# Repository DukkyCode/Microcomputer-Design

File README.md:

# Microcomputer Design
Introduction:
-	The goal of this project is to design, build, and program a single-board computer. It also provides insight into computer architecture

Chip Specification:
- XR68C681CJ-F – DUART: the XR68C681 devices offers a single IC solution for the 68000 family of microprocessors.
- U62256ADK07LLG – RAM: Static RAM 32K x 8-Bit High Speed CMOS 150ns DIP -28
- AT28C256-15PU – ROM: Memory & Data Storage (EEPROM IC EEPROM 256k 50NS 28DIP) 
- Max232E: IC Transceiver 2 channel 16DIP to interface with DUART
- LD1085V50 – Voltage Regulator: Step 9V down to 5V to provide power for the entire board
- JS202011SCQN – Power Switch: Switch to turn on & off power
- B3F-1022 – Reset Button: Simple power button to activate RESET on the buttons
-	A-DS 09 A/KG-T2S – D-SUB connector: create serial communications with the desktop
-	PJ-002B – Barrel Plug: Barrel Connector to connect with power adapter
- ECS-2200B-080: Create 8MHz clock signal for the CPLD & CPU
- ECS-2100AX-036: Create 3.6MHz clock signal for the DUART chips
- 22-28-4061: J-TAG connector to program the CPLD

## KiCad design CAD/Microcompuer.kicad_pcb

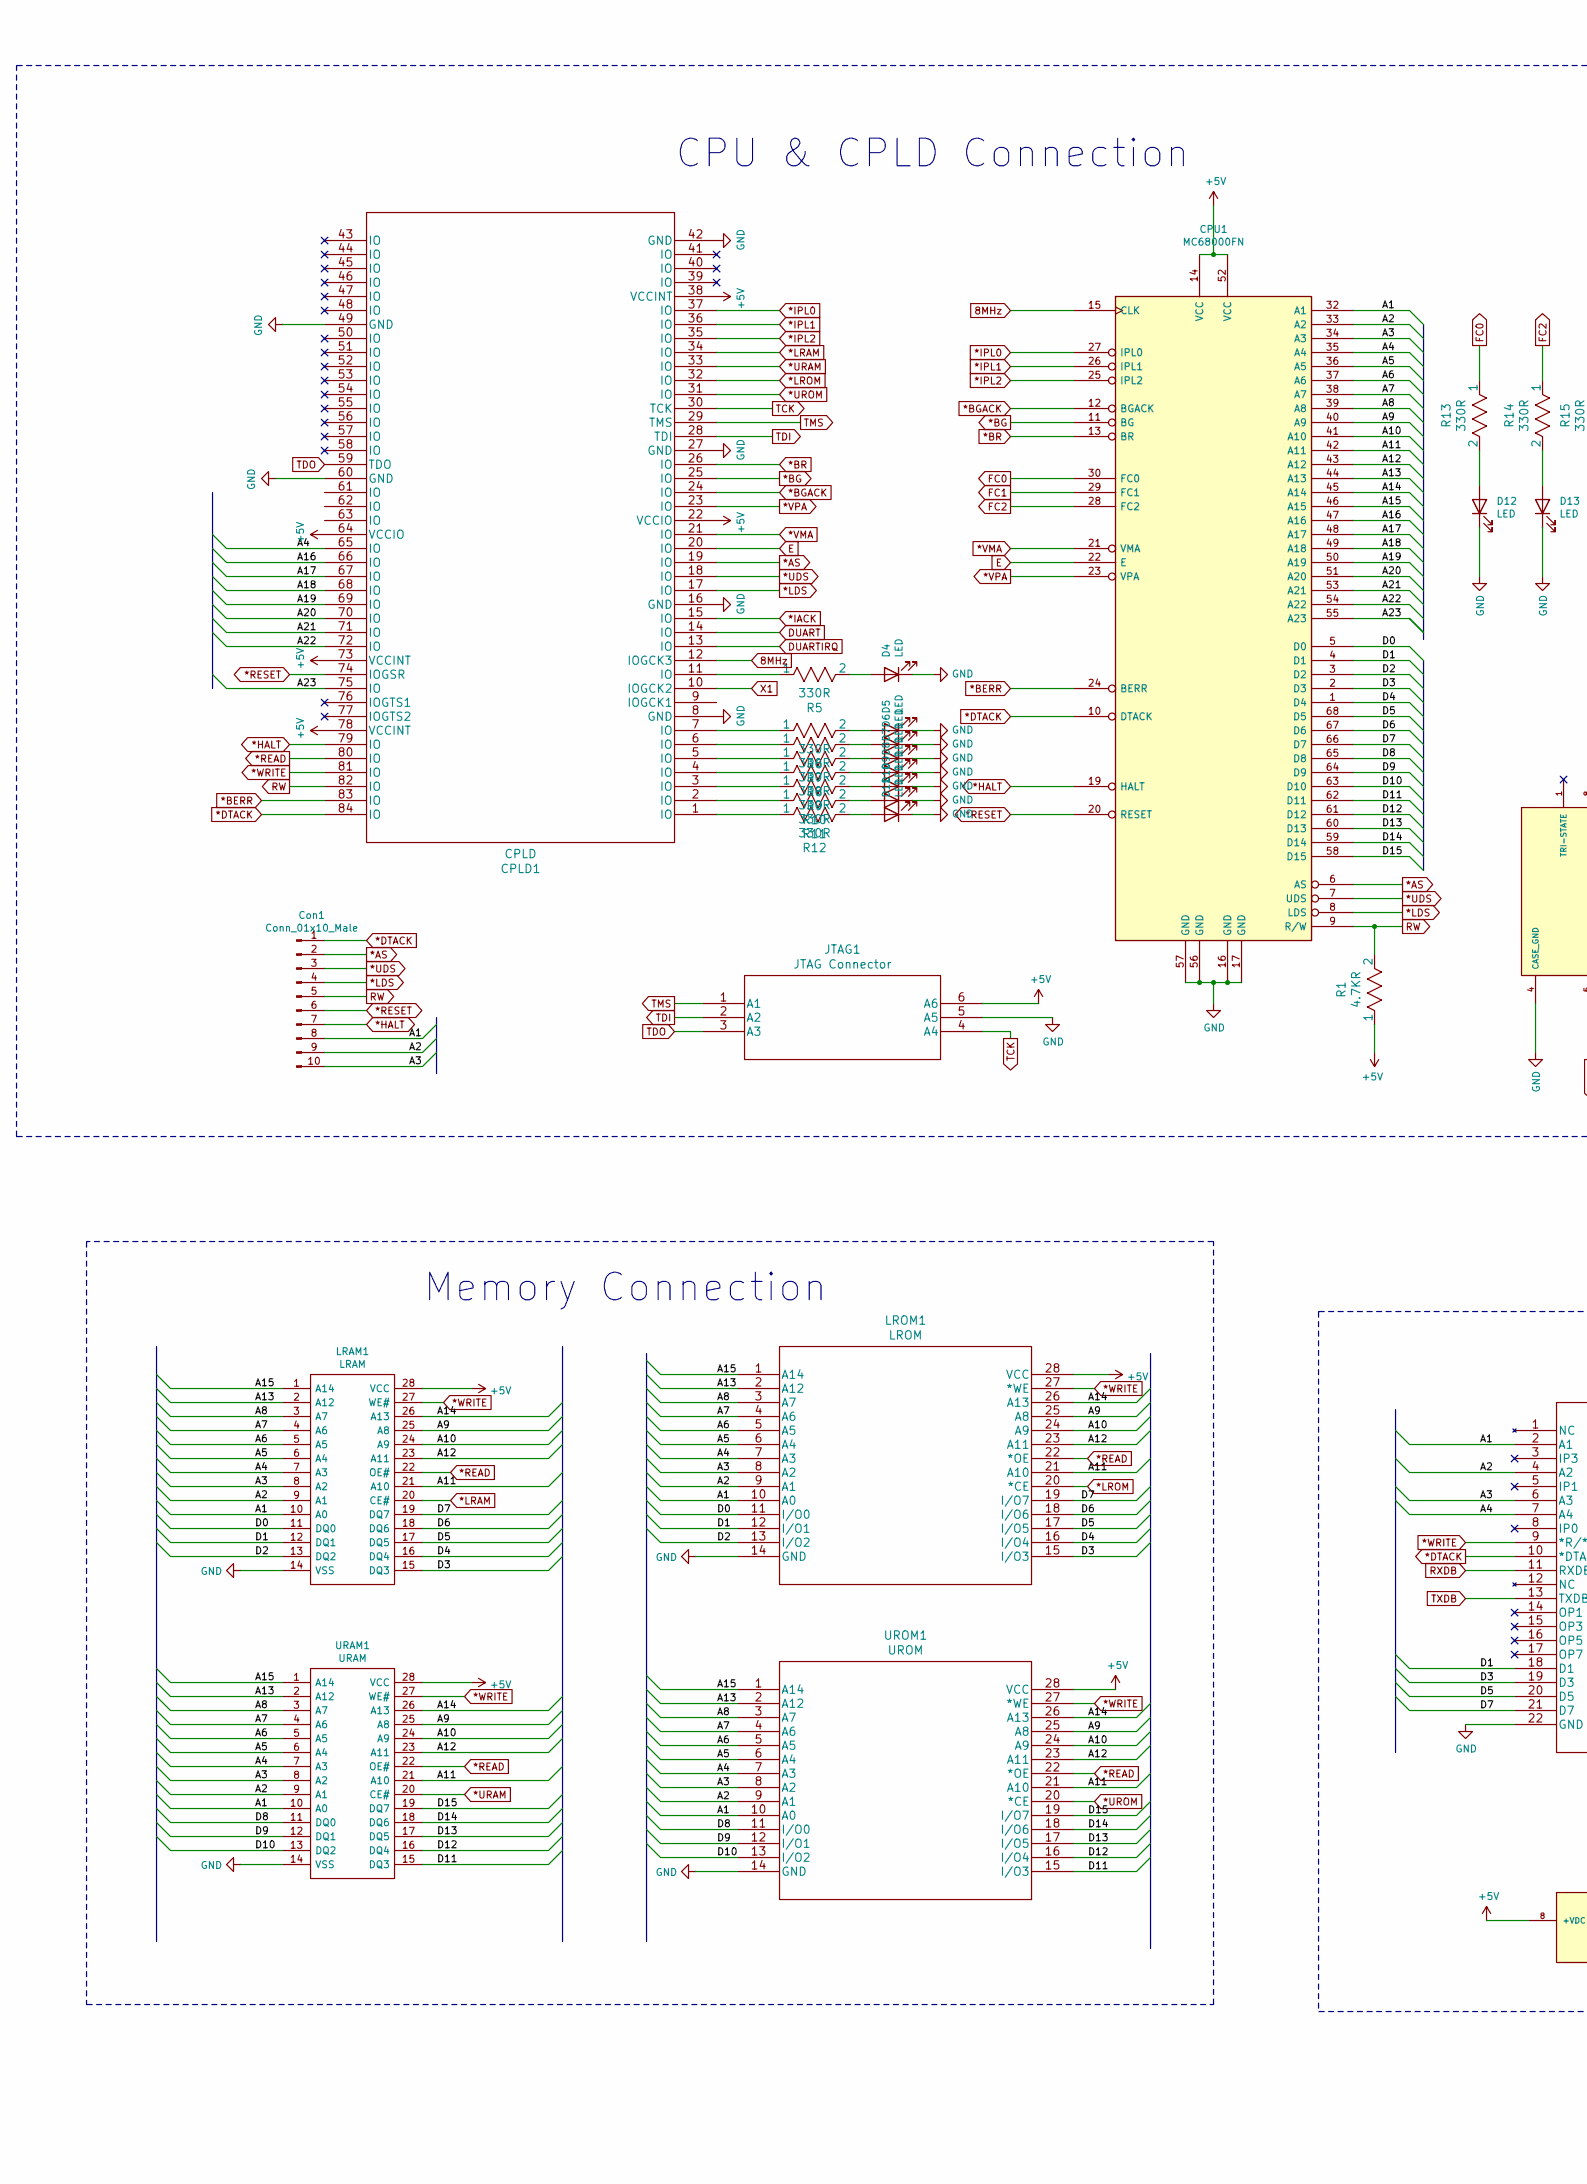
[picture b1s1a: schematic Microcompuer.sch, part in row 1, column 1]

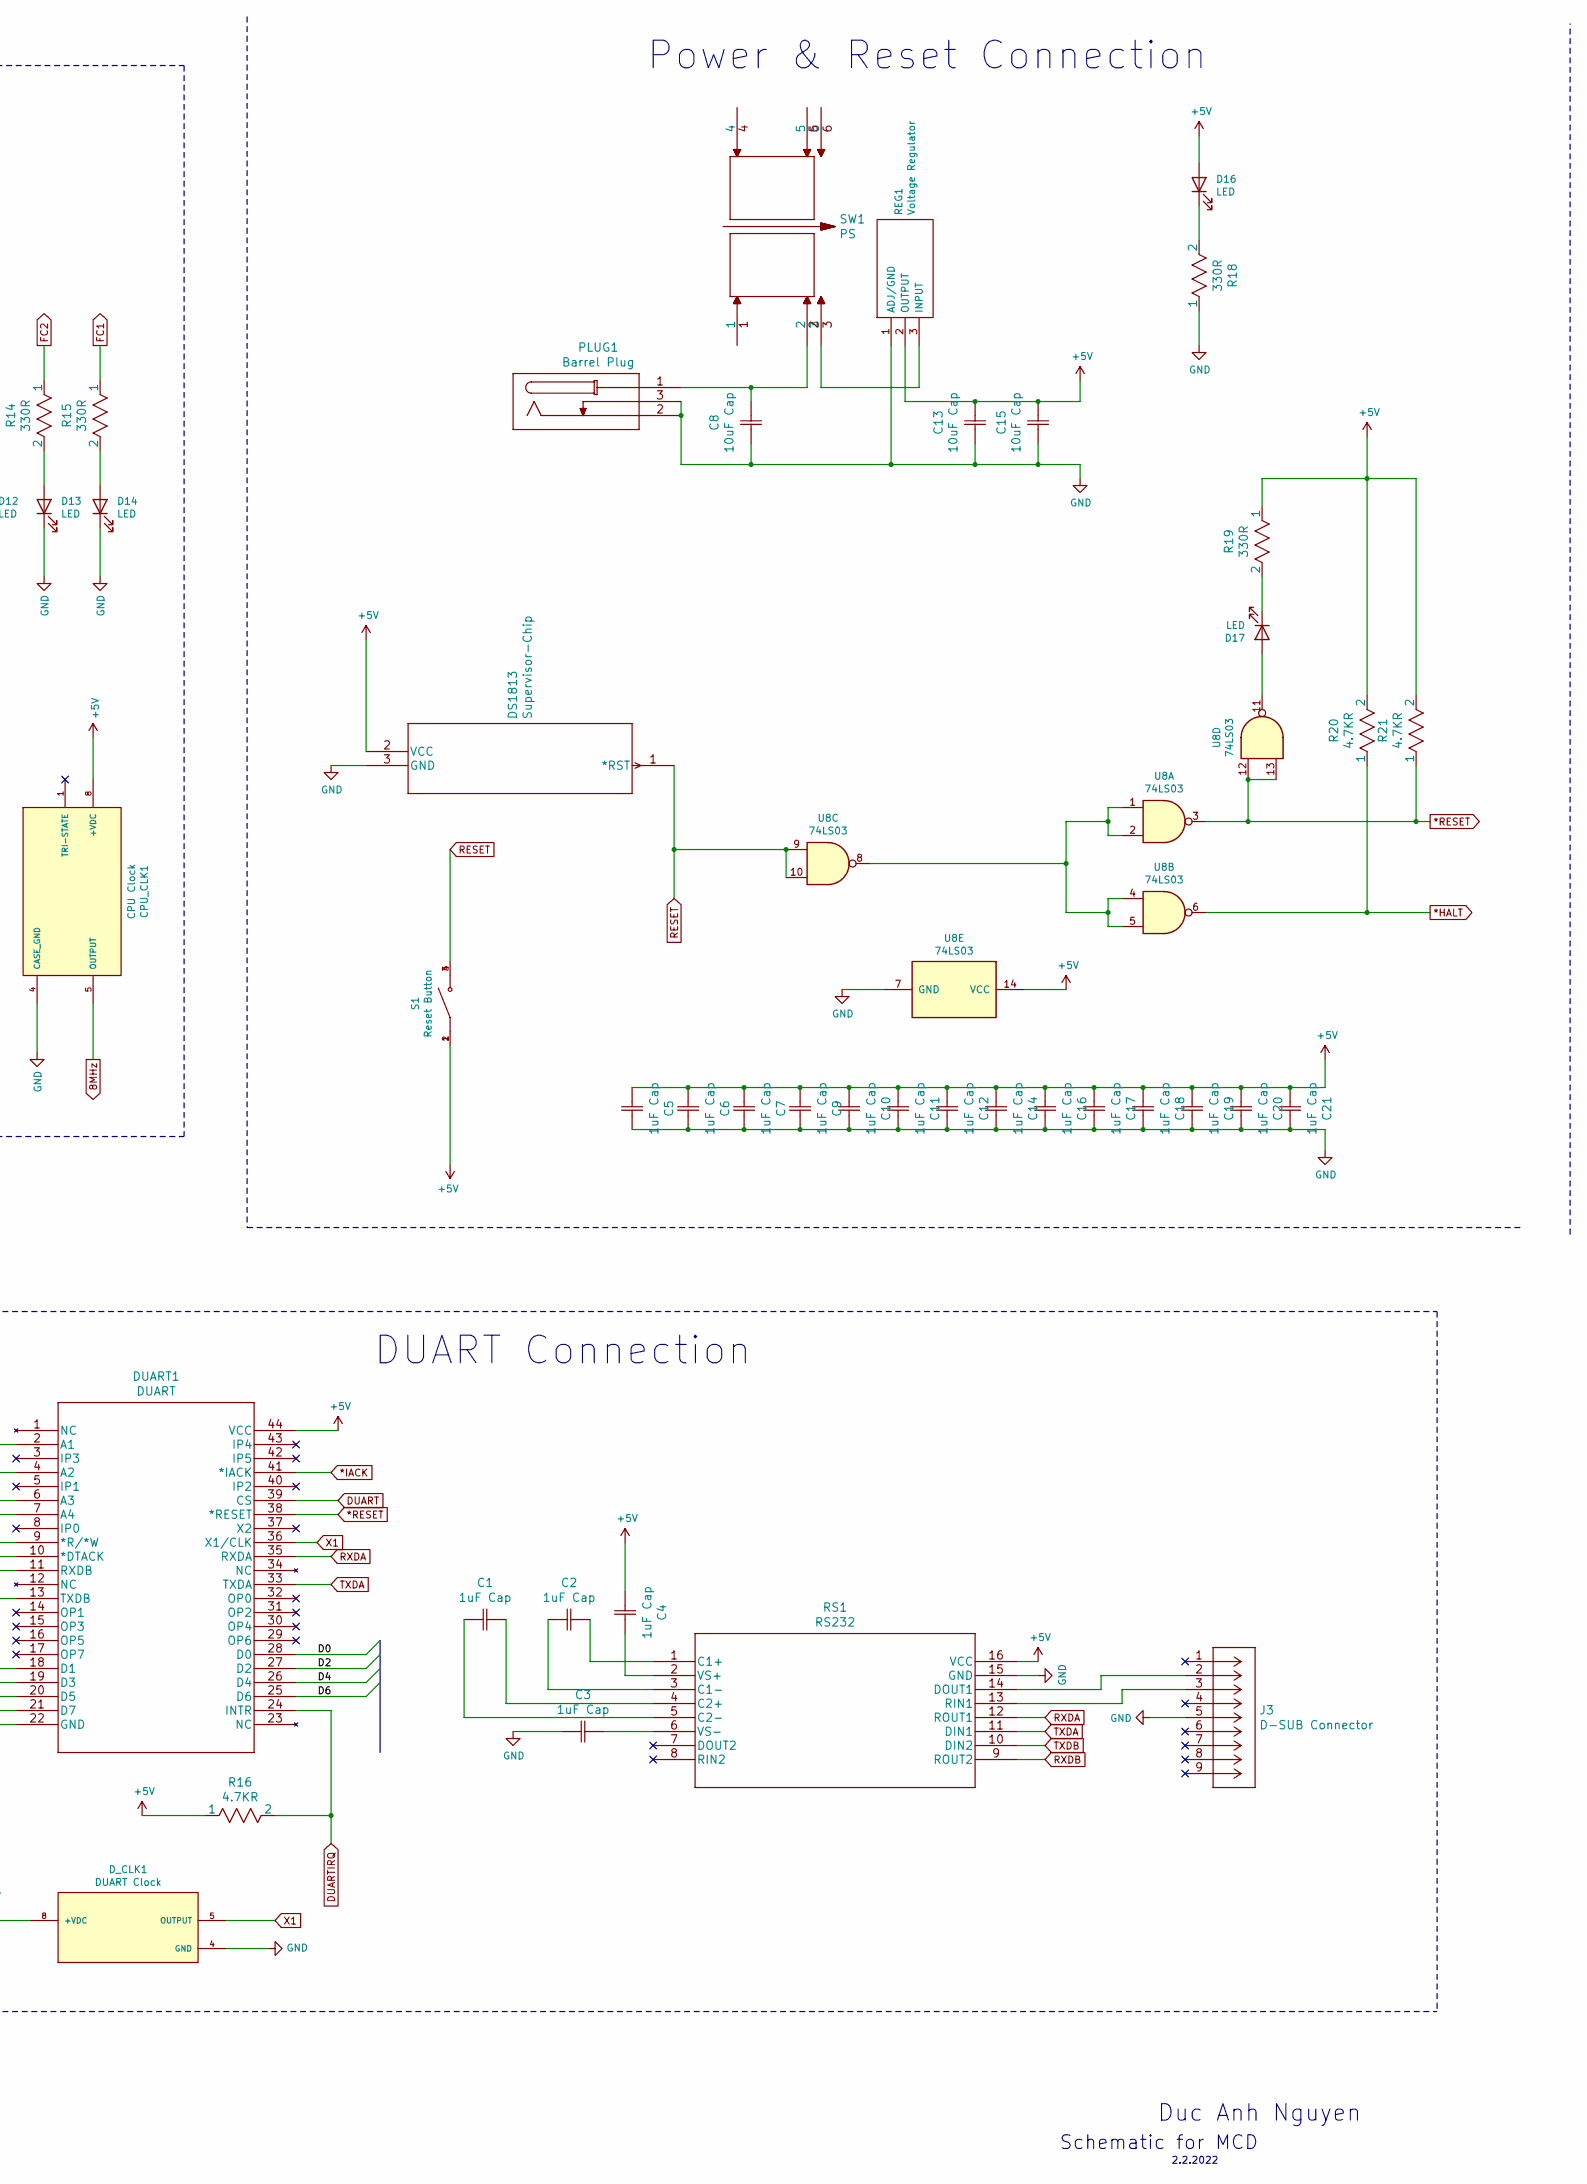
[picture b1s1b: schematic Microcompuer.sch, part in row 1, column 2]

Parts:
C1, C2, C3, C4, C5, C6, C7, C9, C10, C11, C12, C14, C16, C17, C18, C19, C20, C21: 1uF Cap; CC0805KKX7R5BB105
C8, C13, C15: 10uF Cap; CC0805KPX5R5BB106
CPLD1: CPLD; PLCC-84_THT-Socket
CPU1: MC68000FN; PLCC-68_THT-Socket
CPU_CLK1: CPU Clock; OSC_ECS-2200B-080; PARTREV N/A
Con1: Conn_01x10_Male; PinHeader_1x10_P2.54mm_Vertical
D4, D5, D6, D7, D8, D9, D10, D11, D12, D13, D14, D16, D17: LED; LEDC2012X80N
DS1813: Supervisor-Chip; 21-0248A
DUART1: DUART; PLCC-44_THT-Socket
D_CLK1: DUART Clock; OSC_ECS-2100AX-036; PARTREV N/A
J3: D-SUB Connector; DSUB-9_Male_Horizontal_P2.77x2.84mm_EdgePinOffset4.94mm_Hou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
JTAG1: JTAG Connector; 22284061
LRAM1: LRAM; DIP-28_W15.24mm_Socket; Manufacturer_Part_Number AS6C62256-55PCN; Mouser Part Number 913-AS6C62256-55PCN
LROM1: LROM; DIP-28_W15.24mm_Socket
PLUG1: Barrel Plug; BarrelJack_CUI_PJ-102AH_Horizontal
R1, R16, R20, R21: 4.7KR; RC0805FR-074K7L
R5, R6, R7, R8, R9, R10, R11, R12, R13, R14, R15, R18, R19: 330R; RC0805FR-07330RL
REG1: Voltage Regulator; TO255P460X1020X2008-3P; Manufacturer_Part_Number LD1085V50; Mouser Part Number 511-LD1085V50
RS1: RS232; MAX232ECN
S1: Reset Button; SW_B3F-1022; PARTREV O
SW1: PS; JS202011SCQN
U8: 74LS03; SN74LS03N
URAM1: URAM; DIP-28_W15.24mm_Socket; Manufacturer_Part_Number AS6C62256-55PCN; Mouser Part Number 913-AS6C62256-55PCN
UROM1: UROM; DIP-28_W15.24mm_Socket

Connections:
8MHz: CPLD1.12 (IOGCK3), CPU1.15 (CLK), CPU_CLK1.5 (OUTPUT)
*AS: CPLD1.19 (IO), CPU1.6 (AS), Con1.2
*BERR: CPLD1.83 (IO), CPU1.24 (BERR)
*BG: CPLD1.25 (IO), CPU1.11 (BG)
*BGACK: CPLD1.24 (IO), CPU1.12 (BGACK)
*BR: CPLD1.26 (IO), CPU1.13 (BR)
*DTACK: CPLD1.84 (IO), CPU1.10 (DTACK), Con1.1, DUART1.10 (*DTACK)
*HALT: CPLD1.79 (IO), CPU1.19 (HALT), Con1.7, R20.1, U8.6
*IACK: CPLD1.15 (IO), DUART1.41 (*IACK)
*IPL0: CPLD1.37 (IO), CPU1.27 (IPL0)
*IPL1: CPLD1.36 (IO), CPU1.26 (IPL1)
*IPL2: CPLD1.35 (IO), CPU1.25 (IPL2)
*LDS: CPLD1.17 (IO), CPU1.8 (LDS), Con1.4
*LRAM: CPLD1.34 (IO), LRAM1.20 (CE#)
*LROM: CPLD1.32 (IO), LROM1.20 (*CE)
*READ: CPLD1.80 (IO), LRAM1.22 (OE#), LROM1.22 (*OE), URAM1.22 (OE#), UROM1.22 (*OE)
*RESET: CPLD1.74 (IOGSR), CPU1.20 (RESET), Con1.6, DUART1.38 (*RESET), R21.1, U8.3, U8.12, U8.13
*UDS: CPLD1.18 (IO), CPU1.7 (UDS), Con1.3
*URAM: CPLD1.33 (IO), URAM1.20 (CE#)
*UROM: CPLD1.31 (IO), UROM1.20 (*CE)
*VMA: CPLD1.21 (IO), CPU1.21 (VMA)
*VPA: CPLD1.23 (IO), CPU1.23 (VPA)
*WRITE: CPLD1.81 (IO), DUART1.9 (*R/*W), LRAM1.27 (WE#), LROM1.27 (*WE), URAM1.27 (WE#), UROM1.27 (*WE)
/A1: CPU1.32 (A1), Con1.8, DUART1.2 (A1), LRAM1.10 (A0), LROM1.10 (A0), URAM1.10 (A0), UROM1.10 (A0)
/A2: CPU1.33 (A2), Con1.9, DUART1.4 (A2), LRAM1.9 (A1), LROM1.9 (A1), URAM1.9 (A1), UROM1.9 (A1)
/A3: CPU1.34 (A3), Con1.10, DUART1.6 (A3), LRAM1.8 (A2), LROM1.8 (A2), URAM1.8 (A2), UROM1.8 (A2)
/A4: CPLD1.65 (IO), CPU1.35 (A4), DUART1.7 (A4), LRAM1.7 (A3), LROM1.7 (A3), URAM1.7 (A3), UROM1.7 (A3)
/A5: CPU1.36 (A5), LRAM1.6 (A4), LROM1.6 (A4), URAM1.6 (A4), UROM1.6 (A4)
/A6: CPU1.37 (A6), LRAM1.5 (A5), LROM1.5 (A5), URAM1.5 (A5), UROM1.5 (A5)
/A7: CPU1.38 (A7), LRAM1.4 (A6), LROM1.4 (A6), URAM1.4 (A6), UROM1.4 (A6)
/A8: CPU1.39 (A8), LRAM1.3 (A7), LROM1.3 (A7), URAM1.3 (A7), UROM1.3 (A7)
/A9: CPU1.40 (A9), LRAM1.25 (A8), LROM1.25 (A8), URAM1.25 (A8), UROM1.25 (A8)
/A10: CPU1.41 (A10), LRAM1.24 (A9), LROM1.24 (A9), URAM1.24 (A9), UROM1.24 (A9)
/A11: CPU1.42 (A11), LRAM1.21 (A10), LROM1.21 (A10), URAM1.21 (A10), UROM1.21 (A10)
/A12: CPU1.43 (A12), LRAM1.23 (A11), LROM1.23 (A11), URAM1.23 (A11), UROM1.23 (A11)
/A13: CPU1.44 (A13), LRAM1.2 (A12), LROM1.2 (A12), URAM1.2 (A12), UROM1.2 (A12)
/A14: CPU1.45 (A14), LRAM1.26 (A13), LROM1.26 (A13), URAM1.26 (A13), UROM1.26 (A13)
/A15: CPU1.46 (A15), LRAM1.1 (A14), LROM1.1 (A14), URAM1.1 (A14), UROM1.1 (A14)
/A16: CPLD1.66 (IO), CPU1.47 (A16)
/A17: CPLD1.67 (IO), CPU1.48 (A17)
/A18: CPLD1.68 (IO), CPU1.49 (A18)
/A19: CPLD1.69 (IO), CPU1.50 (A19)
/A20: CPLD1.70 (IO), CPU1.51 (A20)
/A21: CPLD1.71 (IO), CPU1.53 (A21)
/A22: CPLD1.72 (IO), CPU1.54 (A22)
/A23: CPLD1.75 (IO), CPU1.55 (A23)
/D0: CPU1.5 (D0), DUART1.28 (D0), LRAM1.11 (DQ0), LROM1.11 (I/O0)
/D1: CPU1.4 (D1), DUART1.18 (D1), LRAM1.12 (DQ1), LROM1.12 (I/O1)
/D2: CPU1.3 (D2), DUART1.27 (D2), LRAM1.13 (DQ2), LROM1.13 (I/O2)
/D3: CPU1.2 (D3), DUART1.19 (D3), LRAM1.15 (DQ3), LROM1.15 (I/O3)
/D4: CPU1.1 (D4), DUART1.26 (D4), LRAM1.16 (DQ4), LROM1.16 (I/O4)
/D5: CPU1.68 (D5), DUART1.20 (D5), LRAM1.17 (DQ5), LROM1.17 (I/O5)
/D6: CPU1.67 (D6), DUART1.25 (D6), LRAM1.18 (DQ6), LROM1.18 (I/O6)
/D7: CPU1.66 (D7), DUART1.21 (D7), LRAM1.19 (DQ7), LROM1.19 (I/O7)
/D8: CPU1.65 (D8), URAM1.11 (DQ0), UROM1.11 (I/O0)
/D9: CPU1.64 (D9), URAM1.12 (DQ1), UROM1.12 (I/O1)
/D10: CPU1.63 (D10), URAM1.13 (DQ2), UROM1.13 (I/O2)
/D11: CPU1.62 (D11), URAM1.15 (DQ3), UROM1.15 (I/O3)
/D12: CPU1.61 (D12), URAM1.16 (DQ4), UROM1.16 (I/O4)
/D13: CPU1.60 (D13), URAM1.17 (DQ5), UROM1.17 (I/O5)
/D14: CPU1.59 (D14), URAM1.18 (DQ6), UROM1.18 (I/O6)
/D15: CPU1.58 (D15), URAM1.19 (DQ7), UROM1.19 (I/O7)
DUART: CPLD1.14 (IO), DUART1.39 (CS)
DUARTIRQ: CPLD1.13 (IO), DUART1.24 (INTR), R16.2
E: CPLD1.20 (IO), CPU1.22 (E)
FC0: CPU1.30 (FC0), R13.1
FC1: CPU1.29 (FC1), R15.1
FC2: CPU1.28 (FC2), R14.1
unnamed: C1.1, RS1.5 (C2-)
unnamed: C1.2, RS1.4 (C2+)
unnamed: C2.1, RS1.3 (C1-)
unnamed: C2.2, RS1.1 (C1+)
unnamed: C3.2, RS1.6 (VS-)
unnamed: C4.2, RS1.2 (VS+)
unnamed: C8.2, PLUG1.1, SW1.2
unnamed: CPLD1.1 (IO), R12.1
unnamed: CPLD1.2 (IO), R11.1
unnamed: CPLD1.3 (IO), R10.1
unnamed: CPLD1.4 (IO), R9.1
unnamed: CPLD1.5 (IO), R8.1
unnamed: CPLD1.6 (IO), R7.1
unnamed: CPLD1.7 (IO), R6.1
unnamed: CPLD1.11 (IO), R5.1
unnamed: D4.2 (A), R5.2
unnamed: D5.2 (A), R6.2
unnamed: D6.2 (A), R7.2
unnamed: D7.2 (A), R8.2
unnamed: D8.2 (A), R9.2
unnamed: D9.2 (A), R10.2
unnamed: D10.2 (A), R11.2
unnamed: D11.2 (A), R12.2
unnamed: D12.2 (A), R13.2
unnamed: D13.2 (A), R14.2
unnamed: D14.2 (A), R15.2
unnamed: D16.1 (K), R18.2
unnamed: D17.1 (K), R19.2
unnamed: D17.2 (A), U8.11
unnamed: DS1813.1 (*RST), S1.3, S1.4, U8.9, U8.10
unnamed: J3.2, RS1.14 (DOUT1)
unnamed: J3.3, RS1.13 (RIN1)
unnamed: REG1.3 (INPUT), SW1.3
unnamed: U8.1, U8.2, U8.4, U8.5, U8.8
RW: CPLD1.82 (IO), CPU1.9 (R/W), Con1.5, R1.2
RXDA: DUART1.35 (RXDA), RS1.12 (ROUT1)
RXDB: DUART1.11 (RXDB), RS1.9 (ROUT2)
TCK: CPLD1.30 (TCK), JTAG1.4 (A4)
TDI: CPLD1.28 (TDI), JTAG1.2 (A2)
TDO: CPLD1.59 (TDO), JTAG1.3 (A3)
TMS: CPLD1.29 (TMS), JTAG1.1 (A1)
TXDA: DUART1.33 (TXDA), RS1.11 (DIN1)
TXDB: DUART1.13 (TXDB), RS1.10 (DIN2)
X1: CPLD1.10 (IOGCK2), DUART1.36 (X1/CLK), D_CLK1.5 (OUTPUT)

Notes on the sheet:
CPU & CPLD Connection
Memory Connection
DUART Connection
Power & Reset Connection
Schematic for MCD
2.2.2022
Duc Anh Nguyen

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
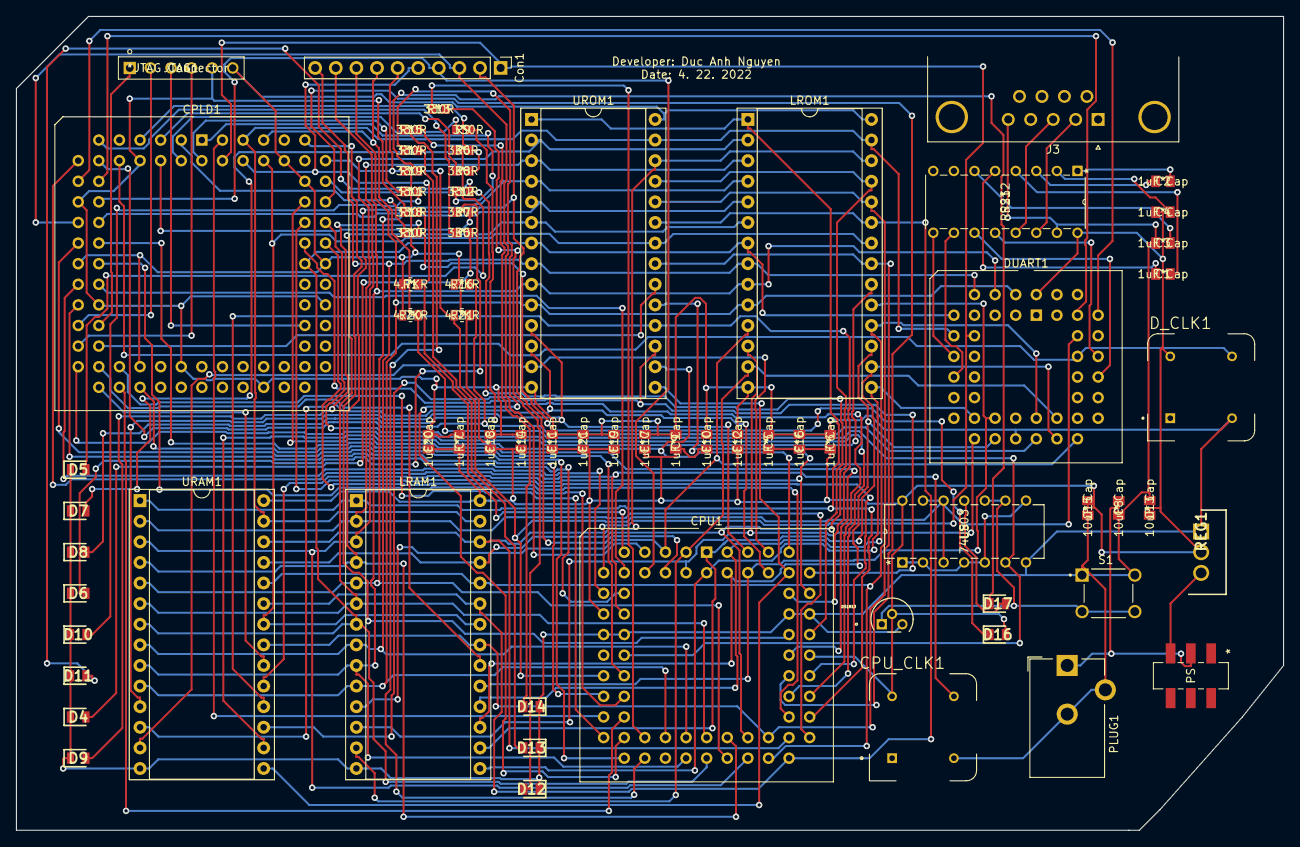
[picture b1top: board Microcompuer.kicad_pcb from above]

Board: 2 copper layers, 156.2 x 100.3 mm, 70 parts (0 on the bottom side), 114 nets.

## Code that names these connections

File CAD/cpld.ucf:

NET D_Line[0]          LOC=P41;
NET D_Line[1]          LOC=P43;
NET D_Line[2]          LOC=P44;
NET D_Line[3]          LOC=P45;
NET D_Line[4]          LOC=P46;
NET D_Line[5]          LOC=P47;
NET D_Line[6]          LOC=P48;
NET D_Line[7]          LOC=P50;
NET D_Line[8]          LOC=P51;
NET D_Line[9]          LOC=P52;
NET D_Line[10]         LOC=P53;
NET D_Line[11]         LOC=P54;
NET D_Line[12]         LOC=P55;
NET D_Line[13]         LOC=P56;
NET D_Line[14]         LOC=P57;
NET D_Line[15]         LOC=P58;

NET A_Upper[0]         LOC=P61;
NET A_Upper[1]         LOC=P62;
NET A_Upper[2]         LOC=P63;
NET A_Upper[3]         LOC=P65;

NET A_Enable[0]        LOC=P66;
NET A_Enable[1]        LOC=P67;

NET A_Lower[0]         LOC=P68;
NET A_Lower[1]         LOC=P69;
NET A_Lower[2]         LOC=P70;
NET A_Lower[3]         LOC=P71;
NET A_Lower[4]         LOC=P72;
NET A_Lower[5]         LOC=P75;

NET RESET_INV          LOC=P74;
NET RESET              LOC=P9;

NET READ_ENABLE        LOC=P80;
NET WRITE_ENABLE       LOC=P81;
NET RW                 LOC=P82;

NET BERR          LOC=P83;
NET DTACK         LOC=P84;

NET IPL0          LOC=P37;
NET IPL1          LOC=P36;
NET IPL2          LOC=P35;

NET LRAM          LOC=P34;
NET URAM          LOC=P33;
NET LROM          LOC=P32;
NET UROM          LOC=P31;

NET BR            LOC=P26;
NET BG            LOC=P25;
NET BGACK         LOC=P24;
NET VPA           LOC=P23;

NET VMA           LOC=P21;
NET E             LOC=P20;
NET AS            LOC=P19;
NET UDS           LOC=P18;
NET LDS           LOC=P17;

NET IACK          LOC=P15;
NET DUART         LOC=P14;
NET DUARTIRQ      LOC=P13;

NET CPU_Clock     LOC=P12;
NET X1            LOC=P10;

NET LED[0]        LOC=P11;
NET LED[1]        LOC=P7;
NET LED[2]        LOC=P6;
NET LED[3]        LOC=P5;
NET LED[4]        LOC=P4;
NET LED[5]        LOC=P3;
NET LED[6]        LOC=P2;
NET LED[7]        LOC=P1;
#Created by Constraints Editor (xc9572-pc84-7) - 2022/03/21
NET "CPU_Clock" TNM_NET = CPU_Clock;
TIMESPEC TS_CPU_Clock = PERIOD "CPU_Clock" 20 ns HIGH 50%;

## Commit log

2023-05-12 Some small changes
2023-05-12 Final Commit

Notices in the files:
parts and their libraries:
Copyright 2021 Accelerated Designs. All rights reserved.
